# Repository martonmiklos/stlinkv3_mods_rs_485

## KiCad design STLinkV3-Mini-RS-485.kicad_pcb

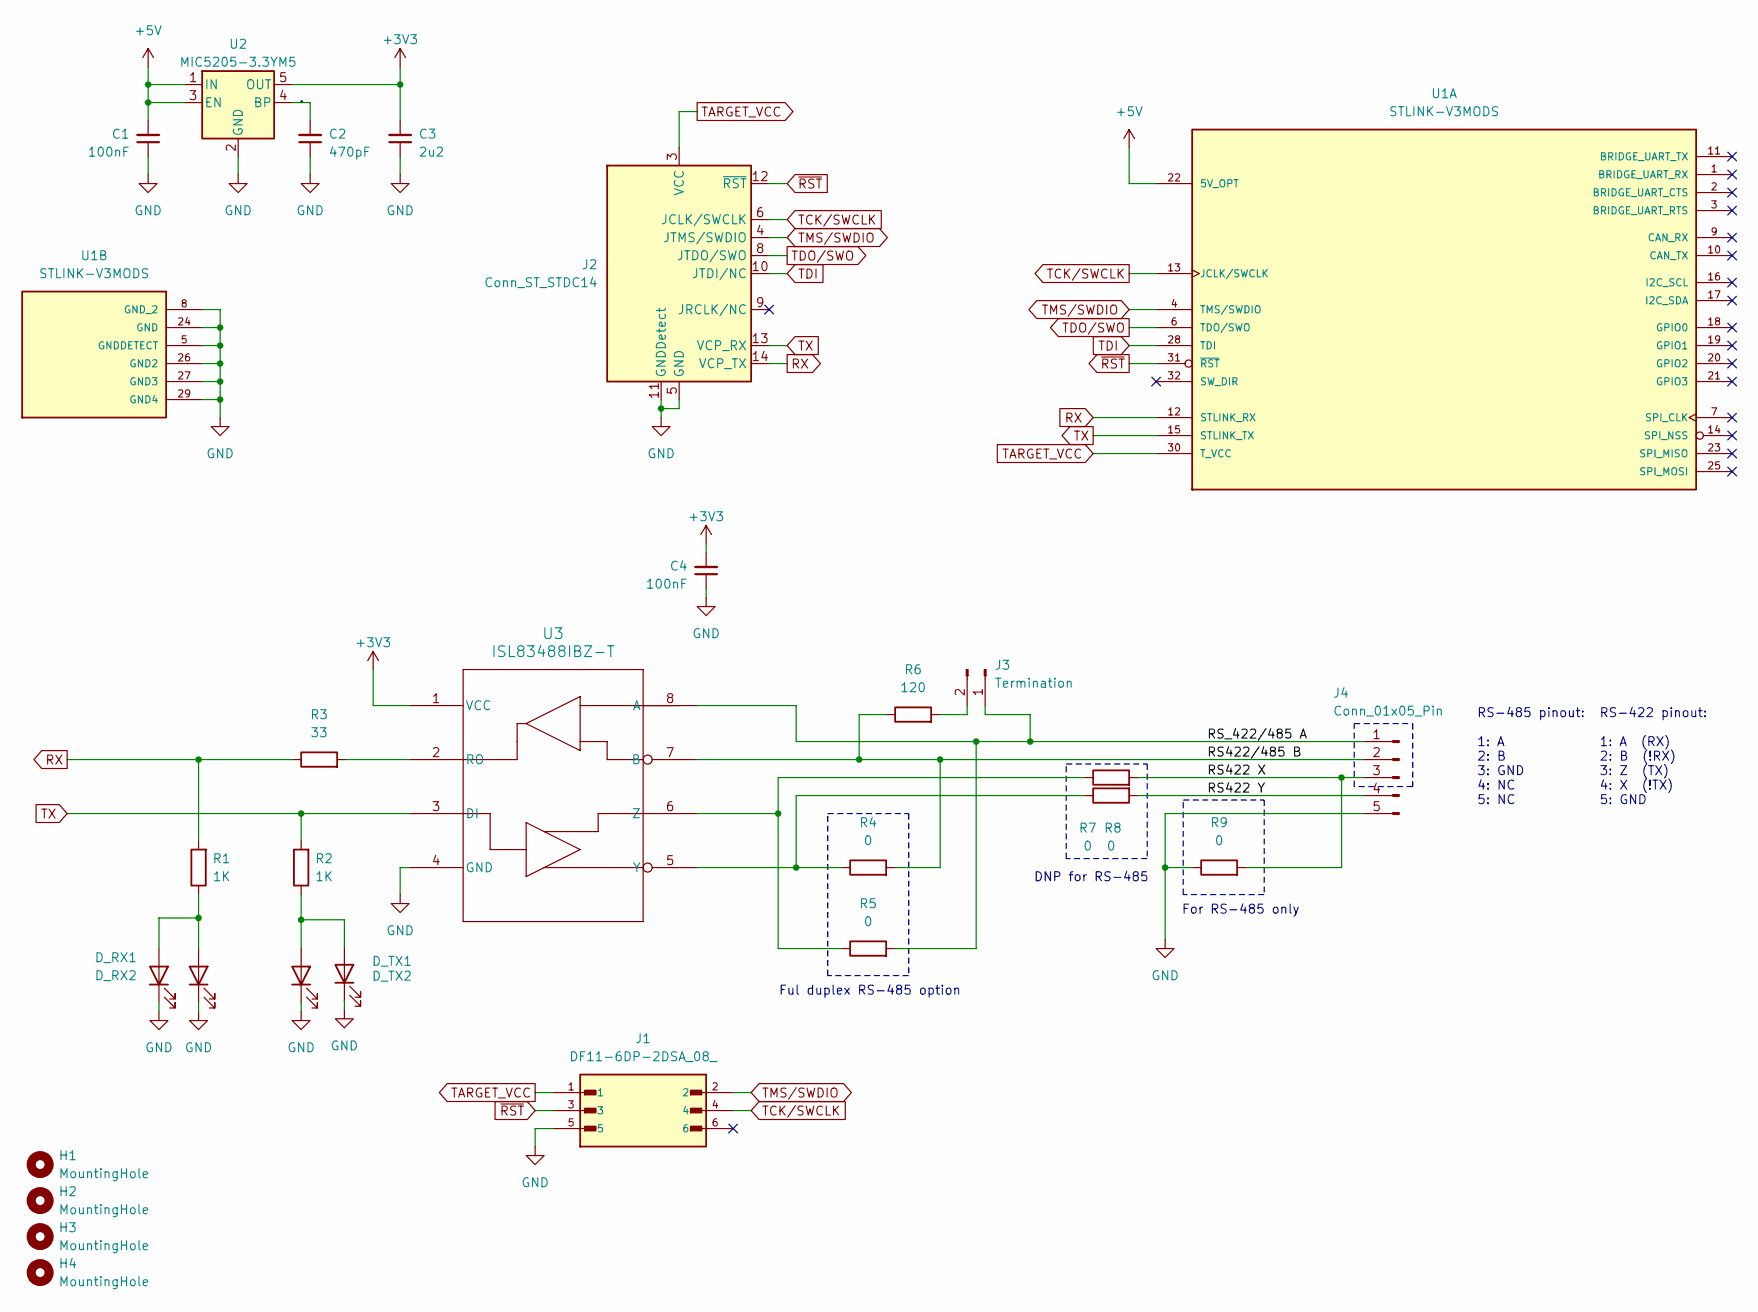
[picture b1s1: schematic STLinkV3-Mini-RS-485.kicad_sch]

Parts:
C1, C4: 100nF; C_0603_1608Metric
C2: 470pF; C_0603_1608Metric
C3: 2u2; C_0603_1608Metric
D_RX1, D_RX2: LED; LED_0603_1608Metric
D_TX1, D_TX2: LED; LED_0603_1608Metric
H1, H2, H3, H4: MountingHole; MountingHole_3.2mm_M3
J1: DF11-6DP-2DSA_08_; HIROSE_DF11-6DP-2DSA_08_; PARTREV 6
J2: Conn_ST_STDC14; PinHeader_2x07_P1.27mm_Vertical_SMD
J3: Termination; PinHeader_1x02_P2.54mm_Vertical
J4: Conn_01x05_Pin; PhoenixContact_MC_1,5_5-G-3.81_1x05_P3.81mm_Horizontal
R1, R2: 1K; R_1206_3216Metric
R3: 33; R_0603_1608Metric
R4, R5, R7, R8, R9: 0; R_0603_1608Metric
R6: 120; R_1206_3216Metric
U1: STLINK-V3MODS; MODULE_STLINK-V3MODS; PARTREV 1
U2: MIC5205-3.3YM5; SOT-23-5
U3: ISL83488IBZ-T; SOIC_488IBZ-T_REN

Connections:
+3V3: C3.2, C4.2, U2.5 (OUT), U3.1 (VCC)
+5V: C1.2, U1.22 (5V_OPT), U2.1 (IN), U2.3 (EN)
/MIC5205_BYPASS: C2.2, U2.4 (BP)
/RS422 X: J4.3, R7.2, R9.2
/RS422 Y: J4.4, R8.2
/RS422/485 B: J4.2, R4.2, R6.1, U3.7 (B)
/RS_422/485 A: J3.1, J4.1, R5.2, U3.8 (A)
GND: C1.1, C2.1, C3.1, C4.1, D_RX1.1 (K), D_RX2.1 (K), D_TX1.1 (K), D_TX2.1 (K), J1.5, J2.5 (GND), J2.7 (GND), J2.11 (GNDDetect), J4.5, R9.1, U1.5 (GNDDETECT), U1.8 (GND_2), U1.24 (GND), U1.26 (GND2), U1.27 (GND3), U1.29 (GND4), U2.2 (GND), U3.4 (GND)
unnamed: D_RX1.2 (A), D_RX2.2 (A), R1.1
unnamed: D_TX1.2 (A), D_TX2.2 (A), R2.1
unnamed: J3.2, R6.2
unnamed: R3.2, U3.2 (RO)
unnamed: R4.1, R8.1, U3.5 (Y)
unnamed: R5.1, R7.1, U3.6 (Z)
RX: J2.14 (VCP_TX), R1.2, R3.1, U1.12 (STLINK_RX)
TARGET_VCC: J1.1, J2.3 (VCC), U1.30 (T_VCC)
TCK/SWCLK: J1.4, J2.6 (JCLK/SWCLK), U1.13 (JCLK/SWCLK)
TDI: J2.10 (JTDI/NC), U1.28 (TDI)
TDO/SWO: J2.8 (JTDO/SWO), U1.6 (TDO/SWO)
TMS/SWDIO: J1.2, J2.4 (JTMS/SWDIO), U1.4 (TMS/SWDIO)
TX: J2.13 (VCP_RX), R2.2, U1.15 (STLINK_TX), U3.3 (DI)
~RST: J1.3, J2.12 (~RST), U1.31 (~RST)

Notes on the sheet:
Ful duplex RS-485 option
RS-422 pinout: 1: A (RX) 2: B (!RX) 3: Z (TX) 4: X (!TX) 5: GND
DNP for RS-485
For RS-485 only
RS-485 pinout: 1: A 2: B 3: GND 4: NC 5: NC

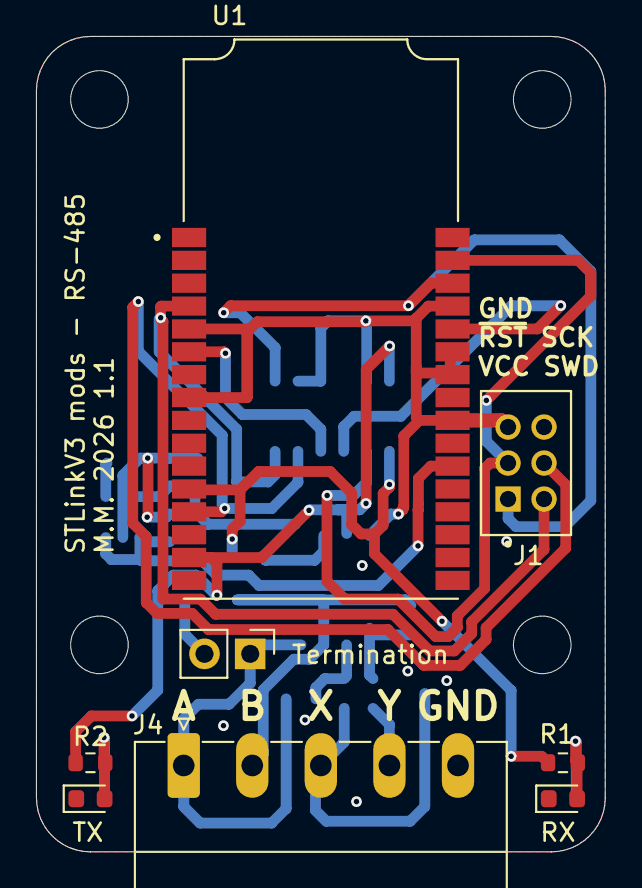
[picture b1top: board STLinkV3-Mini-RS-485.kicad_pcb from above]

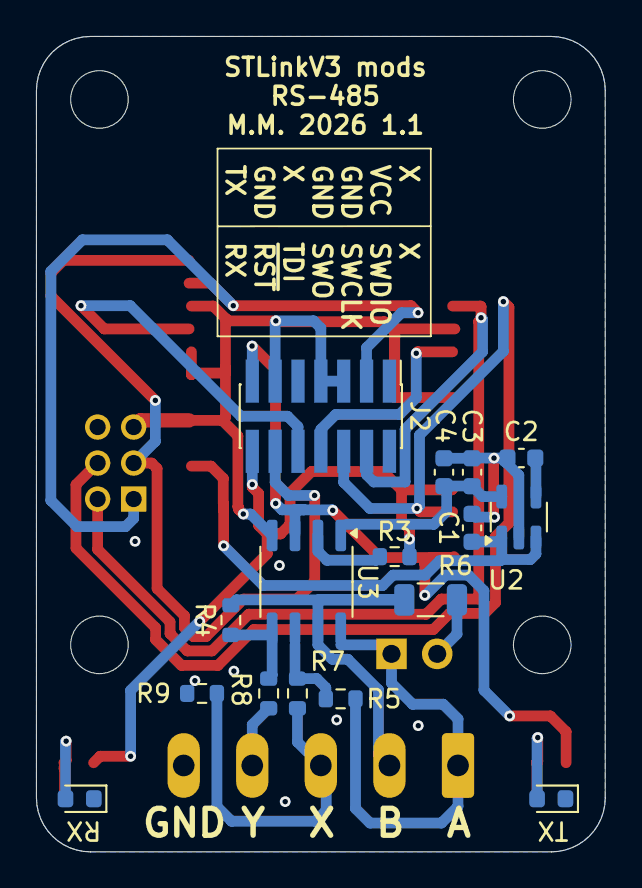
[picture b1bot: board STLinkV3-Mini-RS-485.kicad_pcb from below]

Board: 2 copper layers, 31.6 x 45.3 mm, 28 parts (16 on the bottom side), 22 nets.

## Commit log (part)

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2025-03-09 Save
